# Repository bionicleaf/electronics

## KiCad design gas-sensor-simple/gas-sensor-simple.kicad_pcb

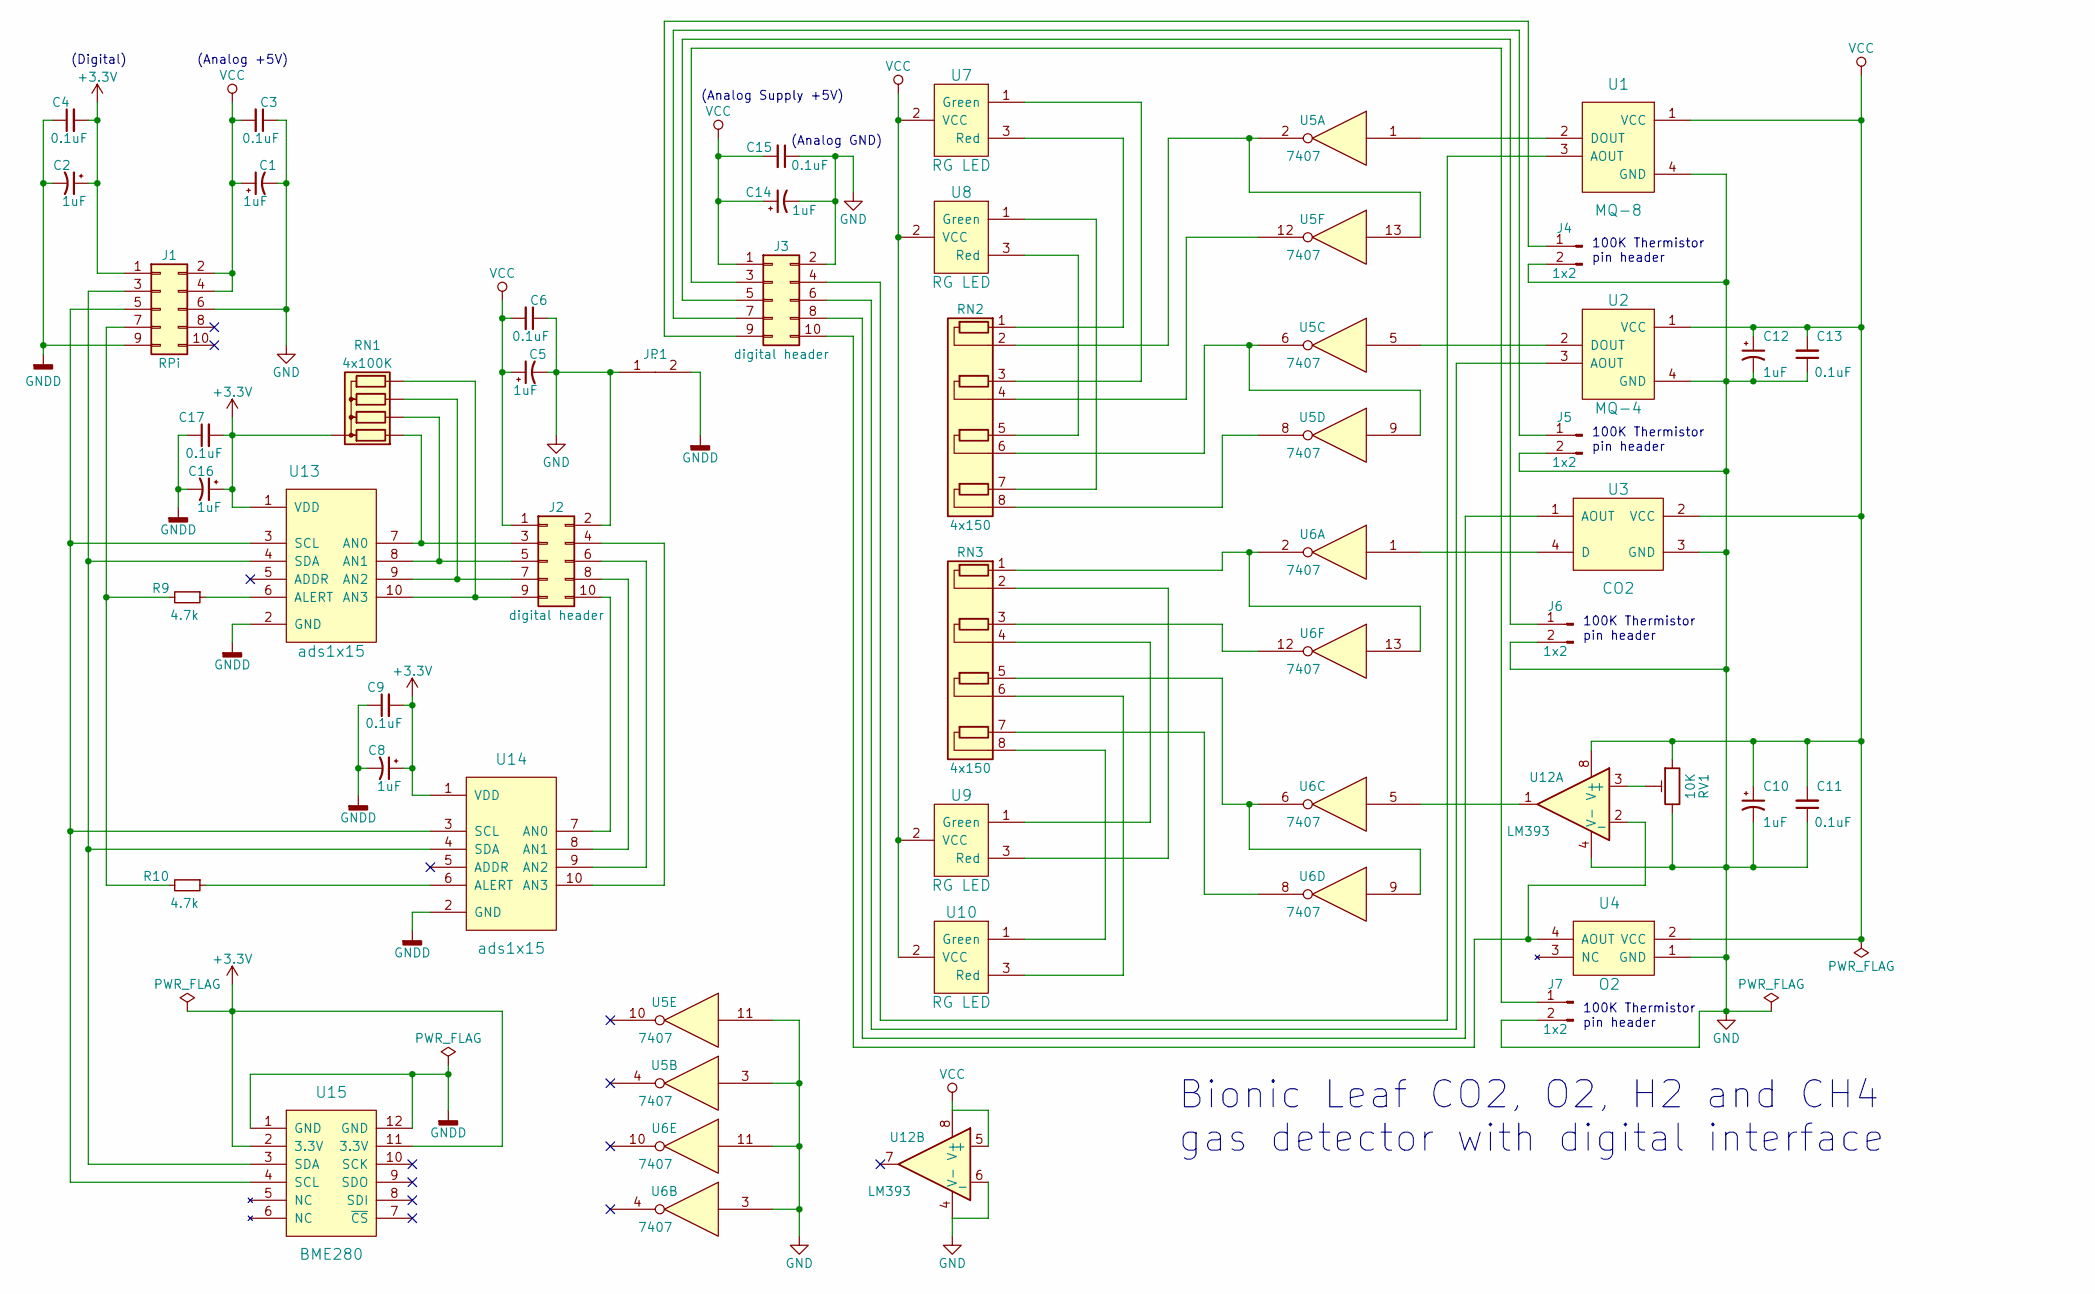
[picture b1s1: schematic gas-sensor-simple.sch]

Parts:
C1, C2, C5, C8, C10, C12, C14, C16: 1uF; CP_Radial_D5.0mm_P2.00mm
C3, C4, C6, C9, C11, C13, C15, C17: 0.1uF; C_Disc_D5.0mm_W2.5mm_P2.50mm
J1: RPi; Pin_Header_Straight_2x05_Pitch2.54mm
J2: digital header; Socket_Strip_Straight_2x05_Pitch2.54mm
J3: digital header; Pin_Header_Straight_2x05_Pitch2.54mm
J4, J5, J6, J7: 1x2; Pin_Header_Straight_1x02_Pitch2.54mm
JP1: .; R_0402_NoSilk
R9, R10: 4.7k; R_Axial_DIN0207_L6.3mm_D2.5mm_P10.16mm_Horizontal
RN1: 4x100K; R_Array_SIP5
RN2, RN3: 4x150; R_Array_SIP8
RV1: 10K; Potentiometer_Trimmer_Piher_PT-10h5_Vertical_Px5.0mm_Py5.0mm
U1: MQ-8; Socket_Strip_Straight_1x04_Pitch2.54mm
U2: MQ-4; Socket_Strip_Straight_1x04_Pitch2.54mm
U3: CO2; Socket_Strip_Straight_1x04_Pitch2.54mm
U4: O2; Socket_Strip_Straight_1x04_Pitch2.54mm
U5, U6: 7407; DIP-14_W7.62mm
U7, U8, U9, U10: RG LED; Socket_Strip_Straight_1x03_Pitch2.54mm
U12: LM393; DIP-8_W7.62mm
U13, U14: ads1x15; Socket_Strip_Straight_1x10_Pitch2.54mm
U15: BME280; DIP-12_W10.16mm

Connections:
+3V3: C2.1, C4.2, C8.1, C9.2, C16.1, C17.2, J1.1, RN1.1 (common), U13.1 (VDD), U14.1 (VDD), U15.2 (3.3V), U15.11 (3.3V)
GND: C1.2, C3.1, C5.2, C6.1, C10.2, C11.1, C12.2, C13.1, C14.2, C15.1, J1.6, J2.2, J3.2, J4.2, J5.2, J6.2, J7.2, JP1.1, RV1.3, U1.4 (GND), U2.4 (GND), U3.3 (GND), U4.1 (GND), U5.3, U5.7 (GND), U5.11, U6.3, U6.7 (GND), U6.11, U12.4 (V-), U12.6 (_); also elsewhere on the board
GNDD: C2.2, C4.1, C8.2, C9.1, C16.2, C17.1, J1.9, JP1.2, U13.2 (GND), U14.2 (GND), U15.1 (GND), U15.12 (GND)
unnamed: J1.3, U13.4 (SDA), U14.4 (SDA), U15.3 (SDA)
unnamed: J1.5, U13.3 (SCL), U14.3 (SCL), U15.4 (SCL)
unnamed: J1.7, R9.2, R10.2
unnamed: J2.3, RN1.2 (R1), U13.7 (AN0)
unnamed: J2.4, U14.10 (AN3)
unnamed: J2.5, RN1.3 (R2), U13.8 (AN1)
unnamed: J2.6, U14.9 (AN2)
unnamed: J2.7, RN1.4 (R3), U13.9 (AN2)
unnamed: J2.8, U14.8 (AN1)
unnamed: J2.9, RN1.5 (R4), U13.10 (AN3)
unnamed: J2.10, U14.7 (AN0)
unnamed: J3.3, J7.1
unnamed: J3.4, U1.3 (AOUT)
unnamed: J3.5, J6.1
unnamed: J3.6, U2.3 (AOUT)
unnamed: J3.7, J5.1
unnamed: J3.8, U3.1 (AOUT)
unnamed: J3.9, J4.1
unnamed 23: J3.10, U4.4 (AOUT), U12.2 (_); also elsewhere on the board
unnamed: R9.1, U13.6 (ALERT)
unnamed: R10.1, U14.6 (ALERT)
unnamed: RN2.1 (R1.1), U7.3 (Red)
unnamed: RN2.2 (R1.2), U5.2, U5.13
unnamed: RN2.3 (R2.1), U7.1 (Green)
unnamed: RN2.4 (R2.2), U5.12
unnamed: RN2.5 (R3.1), U8.3 (Red)
unnamed: RN2.6 (R3.2), U5.6, U5.9
unnamed: RN2.7 (R4.1), U8.1 (Green)
unnamed: RN2.8 (R4.2), U5.8
unnamed: RN3.1 (R1.1), U6.2, U6.13
unnamed: RN3.2 (R1.2), U9.3 (Red)
unnamed: RN3.3 (R2.1), U6.12
unnamed: RN3.4 (R2.2), U9.1 (Green)
unnamed: RN3.5 (R3.1), U6.6, U6.9
unnamed: RN3.6 (R3.2), U10.3 (Red)
unnamed: RN3.7 (R4.1), U6.8
unnamed: RN3.8 (R4.2), U10.1 (Green)
unnamed 42: RV1.2, U12.3 (+); also elsewhere on the board
unnamed: U1.2 (DOUT), U5.1
unnamed: U2.2 (DOUT), U5.5
unnamed: U3.4 (D), U6.1
unnamed 51: U6.5, U12.1; also elsewhere on the board
VCC: C1.1, C3.2, C5.1, C6.2, C10.1, C11.2, C12.1, C13.2, C14.1, C15.2, J1.2, J1.4, J2.1, J3.1, RV1.1, U1.1 (VCC), U2.1 (VCC), U3.2 (VCC), U4.2 (VCC), U5.14 (VCC), U6.14 (VCC), U7.2 (VCC), U8.2 (VCC), U9.2 (VCC), U10.2 (VCC), U12.5 (+), U12.8 (V+); also elsewhere on the board

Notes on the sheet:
Bionic Leaf CO2, O2, H2 and CH4 gas detector with digital interface
(Analog +5V)
(Digital)
(Analog Supply +5V)
(Analog GND)
100K Thermistor pin header

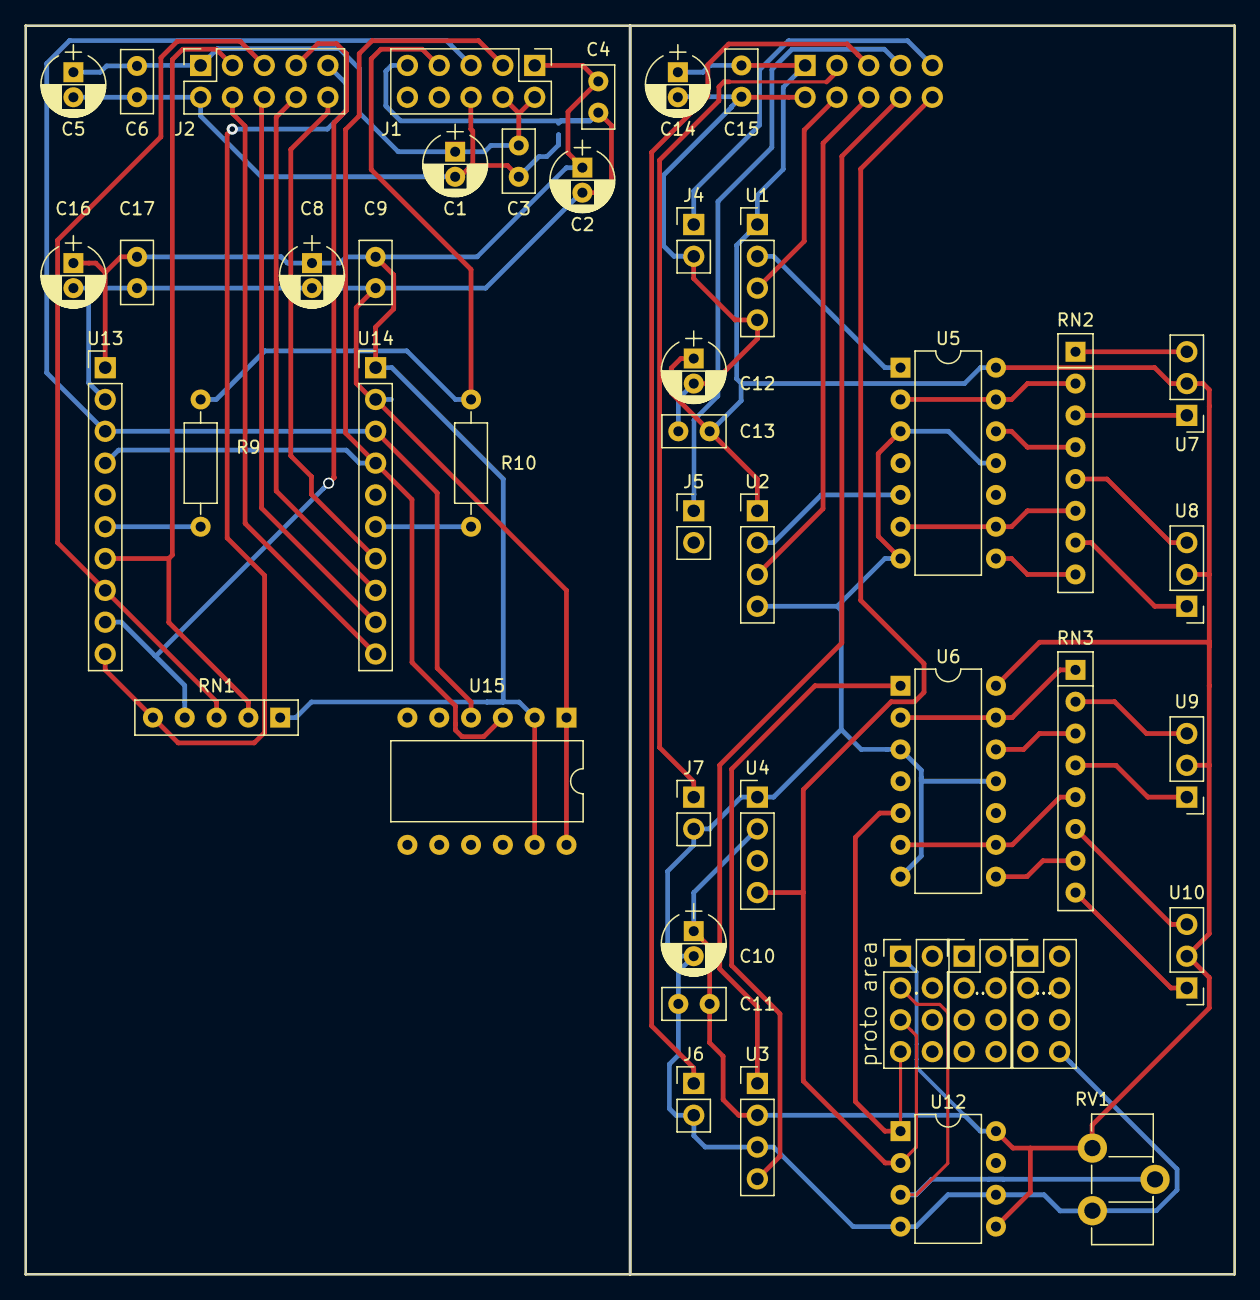
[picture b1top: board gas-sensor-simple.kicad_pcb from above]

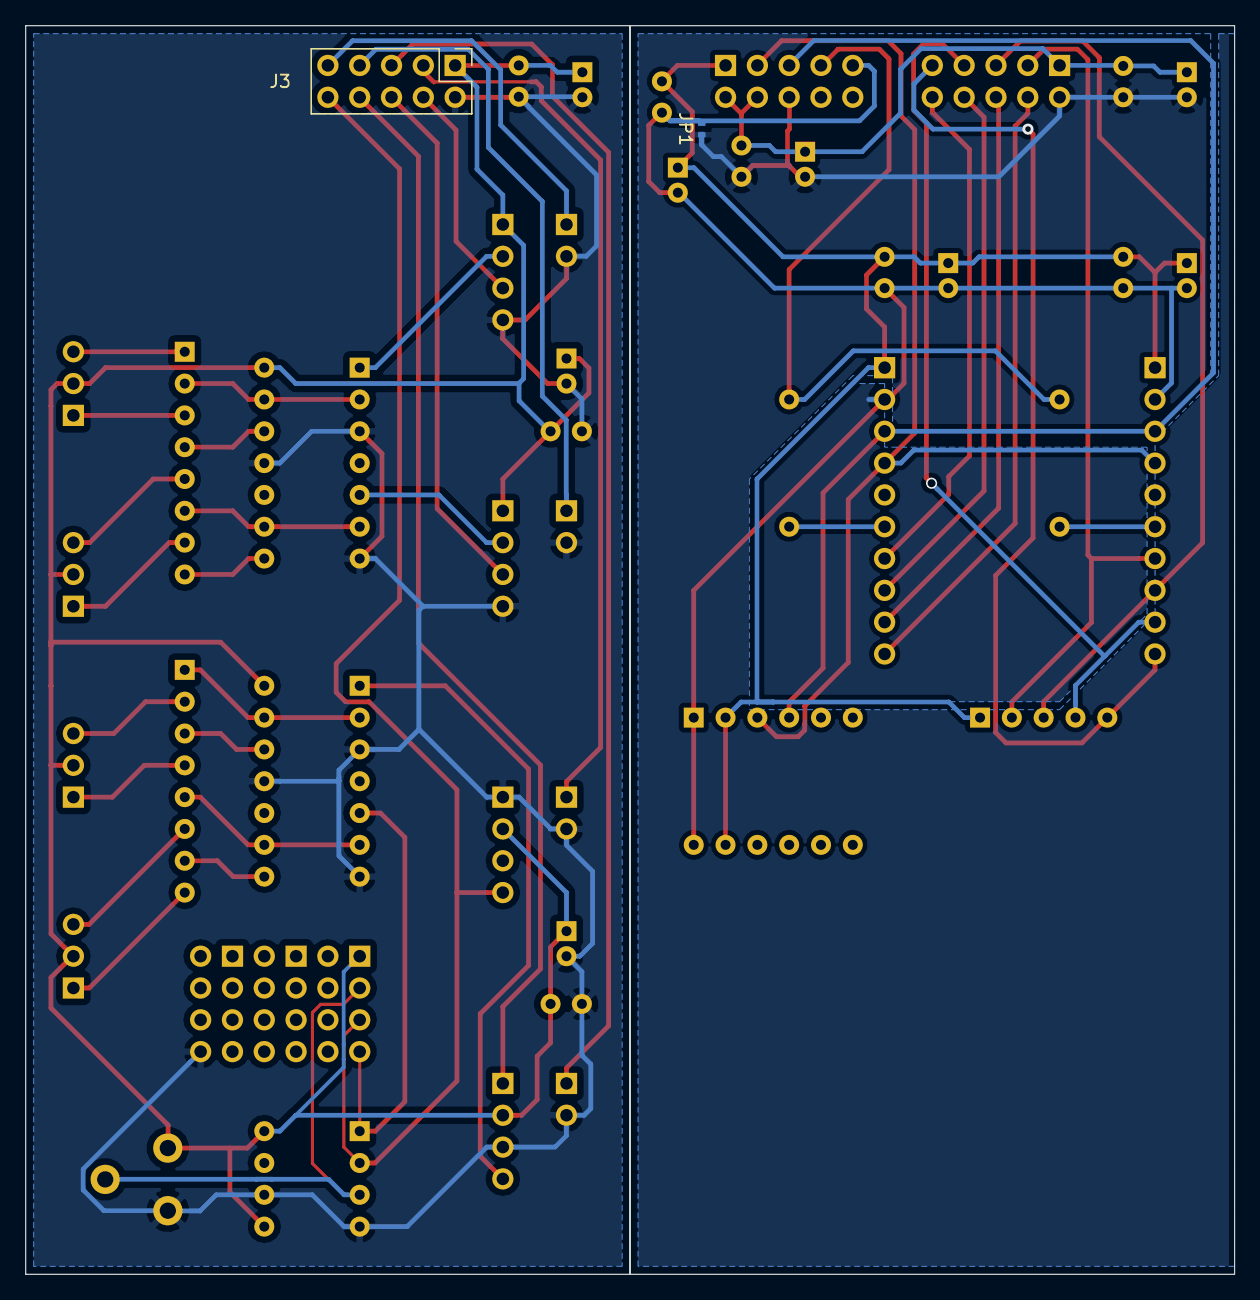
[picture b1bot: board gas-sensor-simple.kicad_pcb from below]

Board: 2 copper layers, 96.5 x 99.7 mm, 47 parts (2 on the bottom side), 46 nets.

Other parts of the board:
., ..: .; Pin_Header_Straight_2x04_Pitch2.54mm
...: ,; Pin_Header_Straight_2x04_Pitch2.54mm

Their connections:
GND: ....8; also elsewhere on the board
unnamed 23: ..5; also elsewhere on the board
unnamed 42: ..3; also elsewhere on the board
unnamed 51: ..7; also elsewhere on the board
VCC: ..1; also elsewhere on the board

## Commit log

2017-09-29 MQx model
2017-09-29 Added datasheets
2017-09-29 Arduino projects
2017-10-06 Plotting and measuring all the things
2017-11-06 First commit KiCAD project for bionic leaf gas sensor. Non-digital version is implemented in half the schematic. Digital interface is added on the left side of the schematic. Still needs resistor val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
2017-11-07 Schematic passes checks. Nearly complete. Need to sort out alert, addr and cs pins on digital side.
2017-11-07 Tweaks to schematic. Add screen capture: schematic.png
2017-11-07 More tweaks. Find out how to fill background of components, so update bionicleaf.lib and schematic.
2017-11-07 Restore rescue.lib since an error box is generated without it.
2017-11-07 Update screen capture
2017-11-07 Begin PCB layout.
2017-11-10 Minor change to pcb
2017-11-10 Add back headers to separate analog board from digital.
2017-11-11 Add 'PCB Design Reduced EMI.pdf'
2017-11-13 Start adding capacitors and improve PCB layout.
2017-11-15 Autorouted version 1 (gas-sensor-simple.kicad_pcb). Start work on version 2 layout (layout.kicad_pcb) moving RPi connector to top of digital board.
2017-11-15 Updated layout.kicad_pcb with RPi connector moved, routed and cleaned up.
2017-11-15 Version of boards that was sent for prototypes
2017-11-29 Add ground planes. Create new gerbers in layout2.gerbers.
2017-11-29 Adjust board edges.
2017-11-29 Adjust board positions to align common edge.
2017-11-29 Latest and greatest keeping generated gerber file extensions.
2018-01-23 Hotplate Schematic
2018-02-19 Update with additions to hotplate and datasheets.
2018-02-20 Move python code to software directory under gas-sensor-simple.
2018-03-03 Add python project inir_ch4 for methane sensor.
2018-03-04 Minor modifications
2018-03-04 Fix project file which had now defunct win32tests.py in the project.
2018-03-07 Add engr data parser to print ppm and temperature.
2018-03-08 Add methanation documents. Change output to print data on one line.
2018-03-10 Add DBD and associated papers.
2018-03-14 More methanation and plasma papers.
2018-03-23 Add data read support for ZE03-H2 sensor in a python class. Example usage at the end of main.py.
2018-03-24 Rename ZE03_H2 to ZE03 since this code works for ZE03-O2 sensor as well.
2018-03-24 Add support for reading T6615 and add datasheet and user manual for this to datasheets folder.
2018-03-24 Add support in main.py for multiple devices at the same time.
2018-03-25 Debug multi-sensor code.
2018-03-26 Add global port definitions in main.py.
2018-03-28 Bug fixes for inir_ch4-only code. Add logging. Argparser is broken under visual studio for some reason. Need to run program from command prompt for now.
